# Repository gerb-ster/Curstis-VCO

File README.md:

# Curtis-VCO

This module is based on the classic CEM3340 VCO chip, although I’m using a AS3340 clone. I’ve took some inspiration from the Maximus VCO design from Thomas Henry. The CEM3340 outputs 3 waveforms with different output levels. To achieve a uniform 10 vpp output around 0 volt, I used a series of op-amps. In the first step the 3 levels is attenuated to 10 vpp, in the next step it’s being offset with 5v to make it swing around 0 volt. I’ve used a trimpot to fine-tune the offset.

The triangle output is then used to ‘wave shape’ a sine output. For this, I also used a classic design from Thomas.

I’ve already made some changes to the PCB design, there was an issue with the power rails on the IO board (hence the bodge wire), some transistor values where wrong, and I made some more room for a good timing cap.

### Update 18-05-2022

Small changes have been made to the io-board to fix an issue with PWM range knob. If you have an older board, you can remove R51 from the ioboard and replace it with a wire and replace R49 with a 91k resistor.

## Status: Finished

- done: first schematic & board design
- done: breadboard and test
- done: design frontpanel
- done: order PCB and build prototype

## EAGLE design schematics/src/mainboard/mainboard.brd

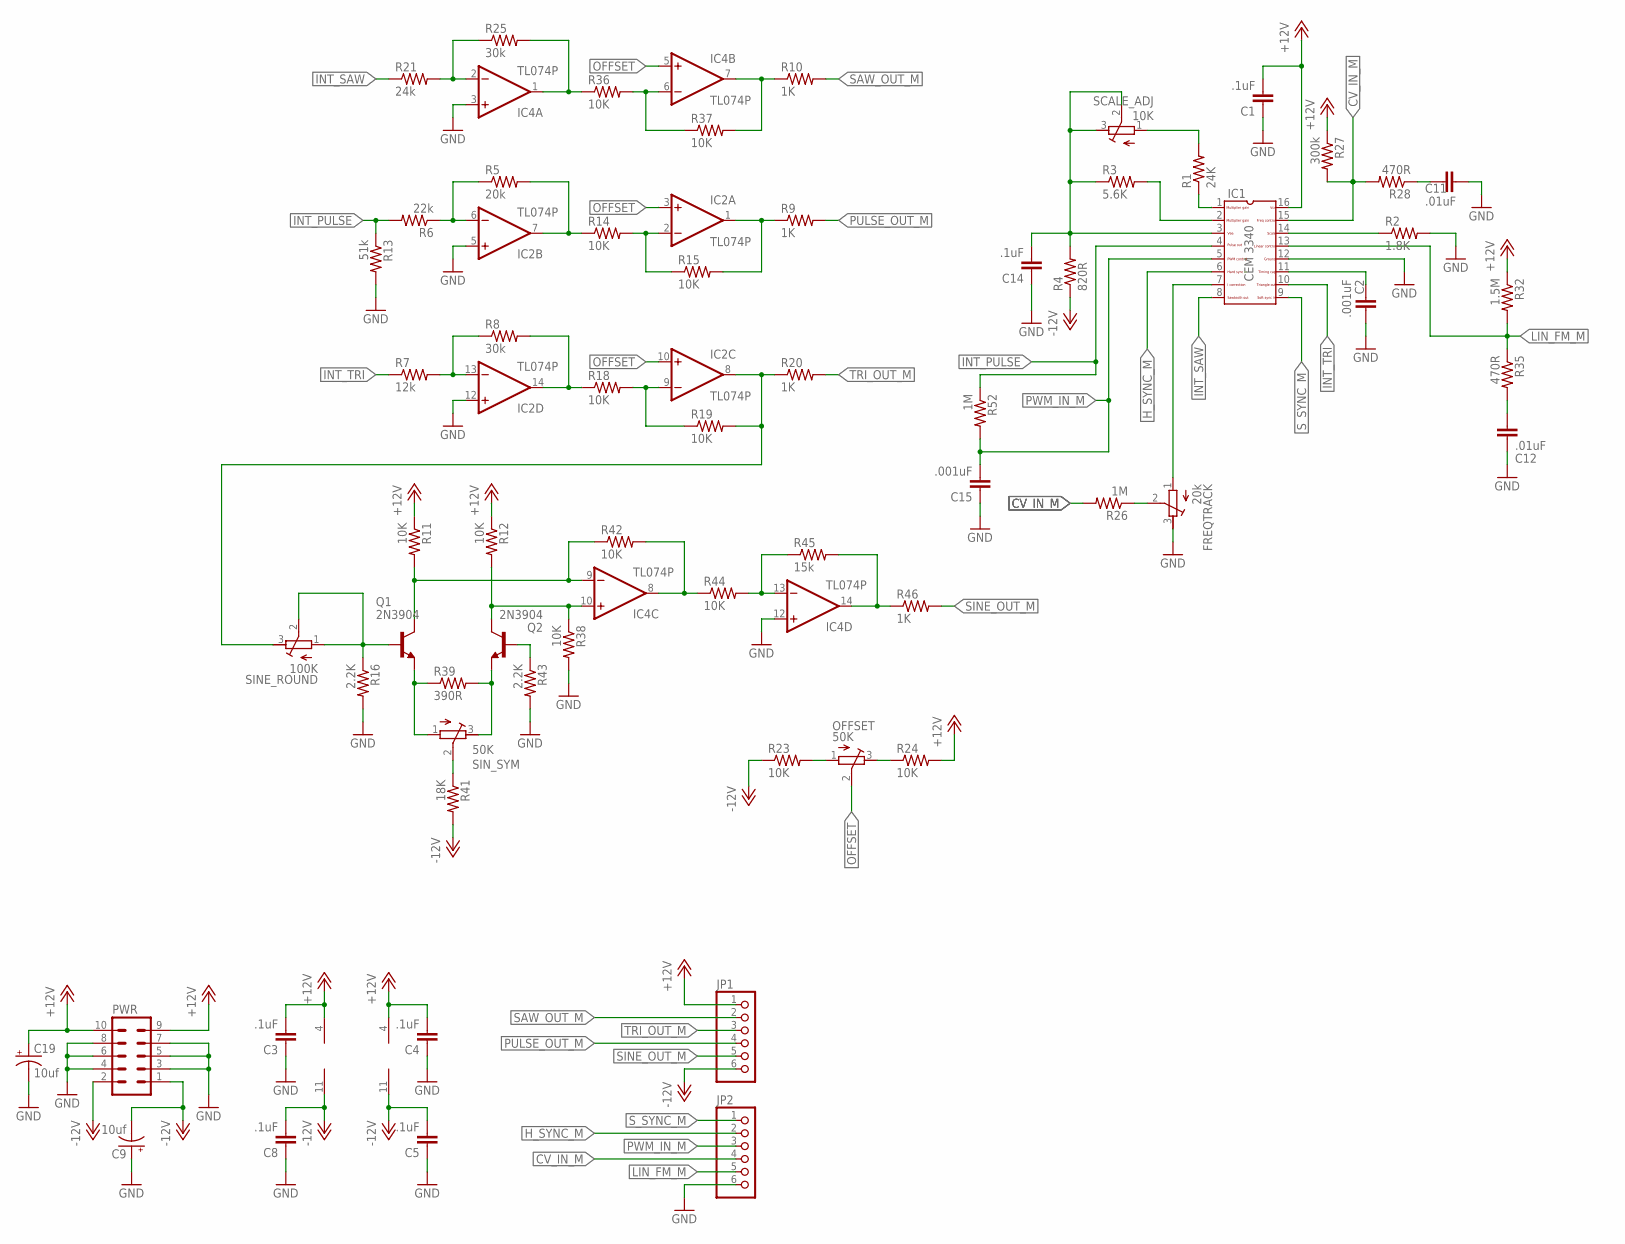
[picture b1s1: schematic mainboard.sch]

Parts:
C1, C3, C4, C5, C8, C14: .1uF; C050-024X044
C2: .001uF; C150-054X183
C9, C19: 10uf; E2,5-5
C11, C12: .01uF; C050-024X044
C15: .001uF; C050-024X044
FREQTRACK: 20k; RTRIM3296W
IC1: CEM3340; DIL16
IC2, IC4: TL074P; DIL14
JP1, JP2: PINHD-1X6; 1X06
OFFSET: 50K; RTRIM3296W
PWR: ML10
Q1, Q2: 2N3904; TO92
R1: 24K; 0207/7
R2: 1.8K; 0207/7
R3: 5.6K; 0207/7
R4: 820R; 0207/7
R5: 20k; 0207/7
R6: 22k; 0207/7
R7: 12k; 0207/7
R8, R25: 30k; 0207/7
R9, R10, R20, R46: 1K; 0207/7
R11, R12, R14, R15, R18, R19, R23, R24, R36, R37, R38, R42, R44: 10K; 0207/7
R13: 51k; 0207/7
R16, R43: 2.2K; 0207/7
R21: 24k; 0207/7
R26, R52: 1M; 0207/7
R27: 300k; 0207/7
R28, R35: 470R; 0207/7
R32: 1.5M; 0207/7
R39: 390R; 0207/7
R41: 18K; 0207/7
R45: 15k; 0207/7
SCALE_ADJ: 10K; RTRIM3296W
SINE_ROUND: 100K; RTRIM3296W
SIN_SYM: 50K; RTRIM3296W

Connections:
+12V: C1.2, C3.2, C4.2, C19.+, IC1.16, IC2.4 (V+), IC4.4 (V+), JP1.1, PWR.9, PWR.10, R11.1, R12.1, R24.2, R27.1, R32.1
-12V: C5.2, C8.2, C9.-, IC2.11 (V-), IC4.11 (V-), JP1.6, PWR.1, PWR.2, R4.1, R23.1, R41.2
CV_IN_M: IC1.15, JP2.4, R26.2, R27.2, R28.2
GND: C1.1, C2.2, C3.1, C4.1, C5.1, C8.1, C9.+, C11.1, C12.2, C14.1, C15.1, C19.-, FREQTRACK.3 (E), IC1.12, IC2.5 (+IN), IC2.12 (+IN), IC4.3 (+IN), IC4.12 (+IN), JP2.6, PWR.3, PWR.4, PWR.5, PWR.6, PWR.7, PWR.8, R2.2, R13.2, R16.2, R38.2, R43.2
HF_CORRECTION: FREQTRACK.1 (A), IC1.7
H_SYNC_M: IC1.6, JP2.2
INT_PULSE: IC1.4, R6.2, R13.1, R52.1
INT_SAW: IC1.8, R21.1
INT_TRI: IC1.10, R7.1
LIN_FM_M: IC1.13, JP2.5, R32.2, R35.1
unnamed: IC1.1, R1.1
unnamed: C2.1, IC1.11
unnamed: IC1.14, R2.1
unnamed: IC1.2, R3.2
unnamed: Q1.2 (B), R16.1, SINE_ROUND.1 (A), SINE_ROUND.2 (S)
unnamed: IC2.6 (-IN), R5.1, R6.1
unnamed: C14.2, IC1.3, R3.1, R4.2, SCALE_ADJ.2 (S), SCALE_ADJ.3 (E)
unnamed: R1.2, SCALE_ADJ.1 (A)
unnamed: IC4.1 (OUT), R25.2, R36.1
unnamed: IC4.9 (-IN), Q1.1 (C), R11.2, R42.1
unnamed: IC2.13 (-IN), R7.2, R8.1
unnamed: IC4.10 (+IN), Q2.1 (C), R12.2, R38.1
unnamed: IC2.14 (OUT), R8.2, R18.1
unnamed: IC2.7 (OUT), R5.2, R14.1
unnamed: IC2.2 (-IN), R14.2, R15.1
unnamed: R41.1, SIN_SYM.2 (S)
unnamed: Q1.3 (E), R39.1, SIN_SYM.1 (A)
unnamed: IC2.9 (-IN), R18.2, R19.1
unnamed: OFFSET.1 (A), R23.2
unnamed: OFFSET.3 (E), R24.1
unnamed: FREQTRACK.2 (S), R26.1
unnamed: C11.2, R28.1
unnamed: IC2.1 (OUT), R9.1, R15.2
unnamed: IC4.6 (-IN), R36.2, R37.1
unnamed: C12.1, R35.2
unnamed: IC2.8 (OUT), R19.2, R20.1, SINE_ROUND.3 (E)
unnamed: Q2.3 (E), R39.2, SIN_SYM.3 (E)
unnamed: IC4.2 (-IN), R21.2, R25.1
unnamed: IC4.8 (OUT), R42.2, R44.1
unnamed: IC4.7 (OUT), R10.1, R37.2
unnamed: Q2.2 (B), R43.1
unnamed: IC4.14 (OUT), R45.2, R46.1
unnamed: IC4.13 (-IN), R44.2, R45.1
OFFSET: IC2.3 (+IN), IC2.10 (+IN), IC4.5 (+IN), OFFSET.2 (S)
PULSE_OUT_M: JP1.4, R9.2
PWM_IN_M: C15.2, IC1.5, JP2.3, R52.2
SAW_OUT_M: JP1.2, R10.2
SINE_OUT_M: JP1.5, R46.2
S_SYNC_M: IC1.9, JP2.1
TRI_OUT_M: JP1.3, R20.2

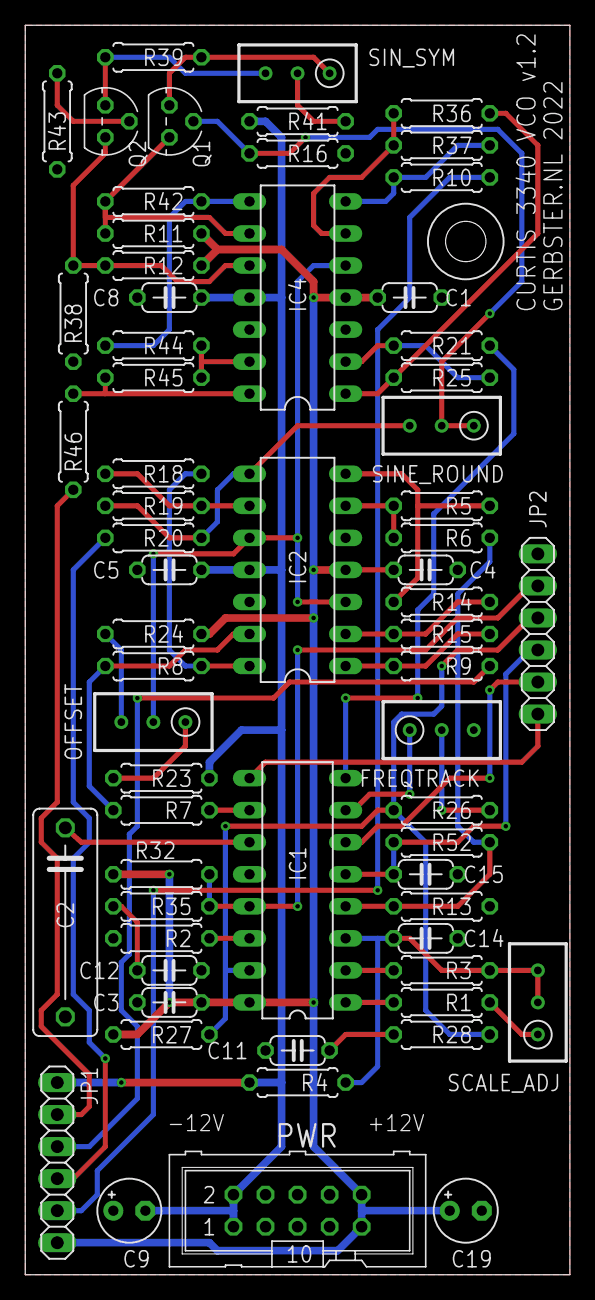
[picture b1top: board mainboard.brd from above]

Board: 2 copper layers, 43.2 x 99.1 mm, 64 parts (0 on the bottom side), 50 nets.

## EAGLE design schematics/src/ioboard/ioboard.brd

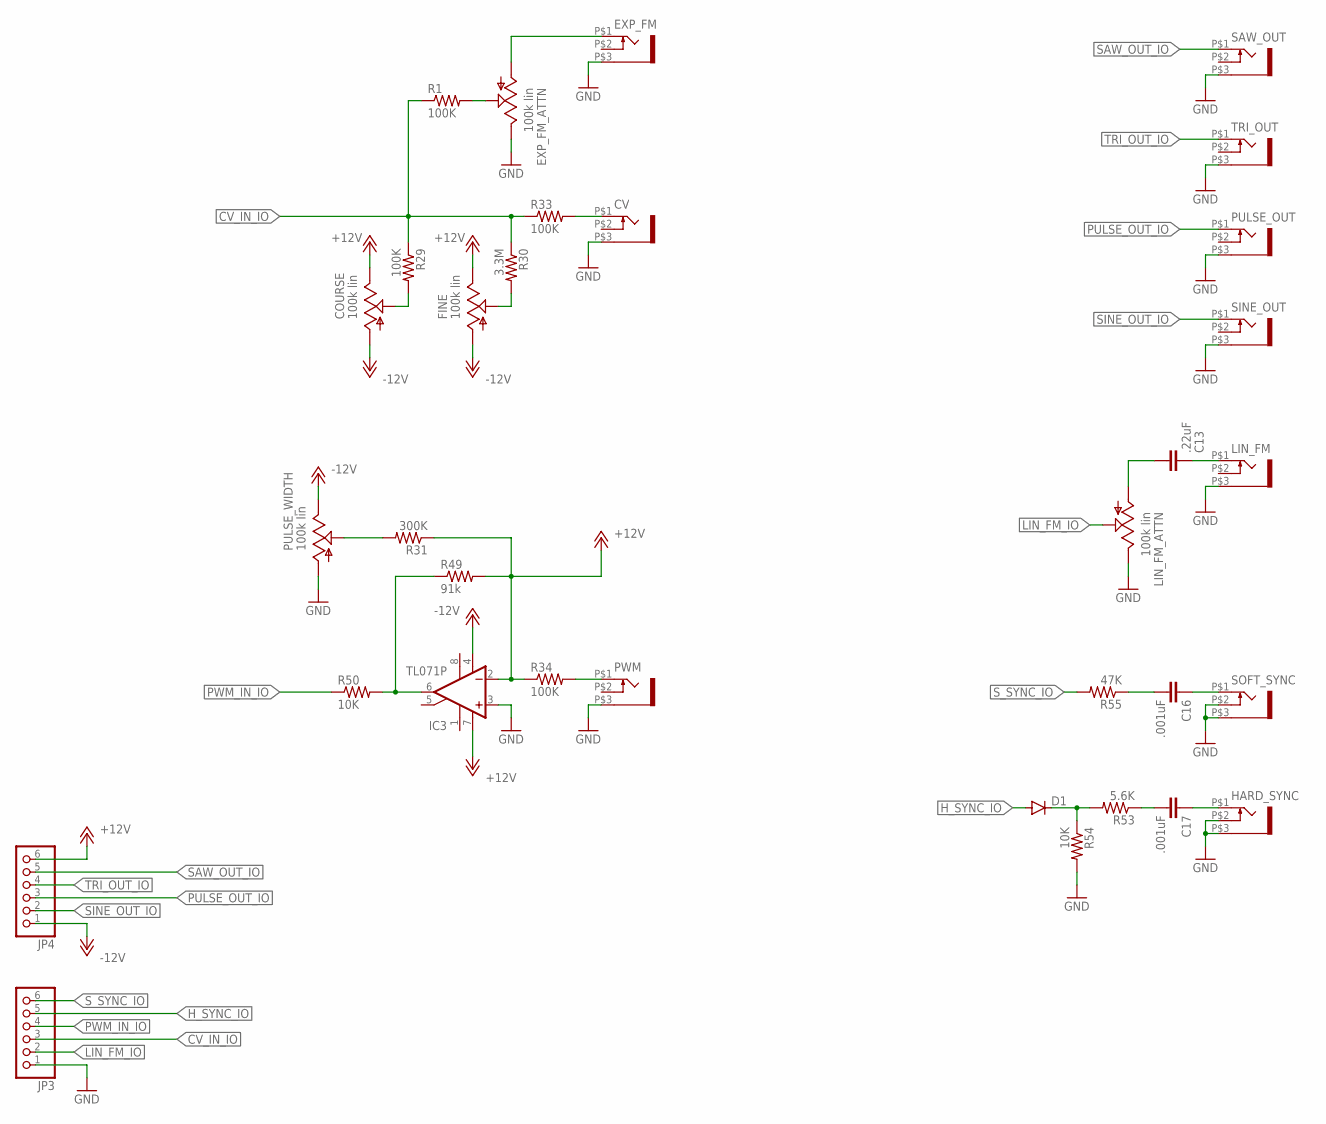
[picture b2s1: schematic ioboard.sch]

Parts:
C13: .22uF; C050-024X044
C16, C17: .001uF; C050-024X044
COURSE: 100k lin; EVUF
CV: WQP-PJ301M-12_JACK
D1: 1N4148DO35-7; DO35-7
EXP_FM: WQP-PJ301M-12_JACK
EXP_FM_ATTN: 100k lin; EVUF
FINE: 100k lin; EVUF
HARD_SYNC: WQP-PJ301M-12_JACK
IC3: TL071P; DIL08
JP3, JP4: PINHD-1X6; 1X06
LIN_FM: WQP-PJ301M-12_JACK
LIN_FM_ATTN: 100k lin; EVUF
PULSE_OUT: WQP-PJ301M-12_JACK
PULSE_WIDTH: 100k lin; EVUF
PWM: WQP-PJ301M-12_JACK
R1, R29, R33, R34: 100K; 0207/7
R30: 3.3M; 0207/7
R31: 300K; 0207/7
R49: 91k; 0207/7
R50, R54: 10K; 0207/7
R53: 5.6K; 0207/7
R55: 47K; 0207/7
SAW_OUT: WQP-PJ301M-12_JACK
SINE_OUT: WQP-PJ301M-12_JACK
SOFT_SYNC: WQP-PJ301M-12_JACK
TRI_OUT: WQP-PJ301M-12_JACK

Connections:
+12V: COURSE.3 (E), FINE.3 (E), IC3.2 (-IN), IC3.7 (V+), JP4.6, R31.1, R34.1, R49.2
-12V: COURSE.1 (A), FINE.1 (A), IC3.4 (V-), JP4.1, PULSE_WIDTH.3 (E)
CV_IN_IO: JP3.3, R1.1, R29.1, R30.1, R33.1
GND: CV.P$3 (1), EXP_FM.P$3 (1), EXP_FM_ATTN.3 (E), HARD_SYNC.P$2 (3), HARD_SYNC.P$3 (1), IC3.3 (+IN), JP3.1, LIN_FM.P$3 (1), LIN_FM_ATTN.3 (E), PULSE_OUT.P$3 (1), PULSE_WIDTH.1 (A), PWM.P$3 (1), R54.2, SAW_OUT.P$3 (1), SINE_OUT.P$3 (1), SOFT_SYNC.P$2 (3), SOFT_SYNC.P$3 (1), TRI_OUT.P$3 (1)
H_SYNC_IO: D1.A, JP3.5
LIN_FM_IO: EXP_FM_ATTN.2 (S), JP3.2, LIN_FM_ATTN.2 (S), R1.2
unnamed: EXP_FM.P$1 (2), EXP_FM_ATTN.1 (A)
unnamed: COURSE.2 (S), R29.2
unnamed: FINE.2 (S), R30.2
unnamed: CV.P$1 (2), R33.2
unnamed: PWM.P$1 (2), R34.2
unnamed: PULSE_WIDTH.2 (S), R31.2
unnamed: C13.2, LIN_FM.P$1 (2)
unnamed: C13.1, LIN_FM_ATTN.1 (A)
unnamed: C16.1, SOFT_SYNC.P$1 (2)
unnamed: IC3.6 (OUT), R49.1, R50.2
unnamed: C16.2, R55.1
unnamed: C17.1, HARD_SYNC.P$1 (2)
unnamed: C17.2, R53.1
unnamed: D1.C, R53.2, R54.1
PULSE_OUT_IO: JP4.3, PULSE_OUT.P$1 (2)
PWM_IN_IO: JP3.4, R50.1
SAW_OUT_IO: JP4.5, SAW_OUT.P$1 (2)
SINE_OUT_IO: JP4.2, SINE_OUT.P$1 (2)
S_SYNC_IO: JP3.6, R55.2
TRI_OUT_IO: JP4.4, TRI_OUT.P$1 (2)

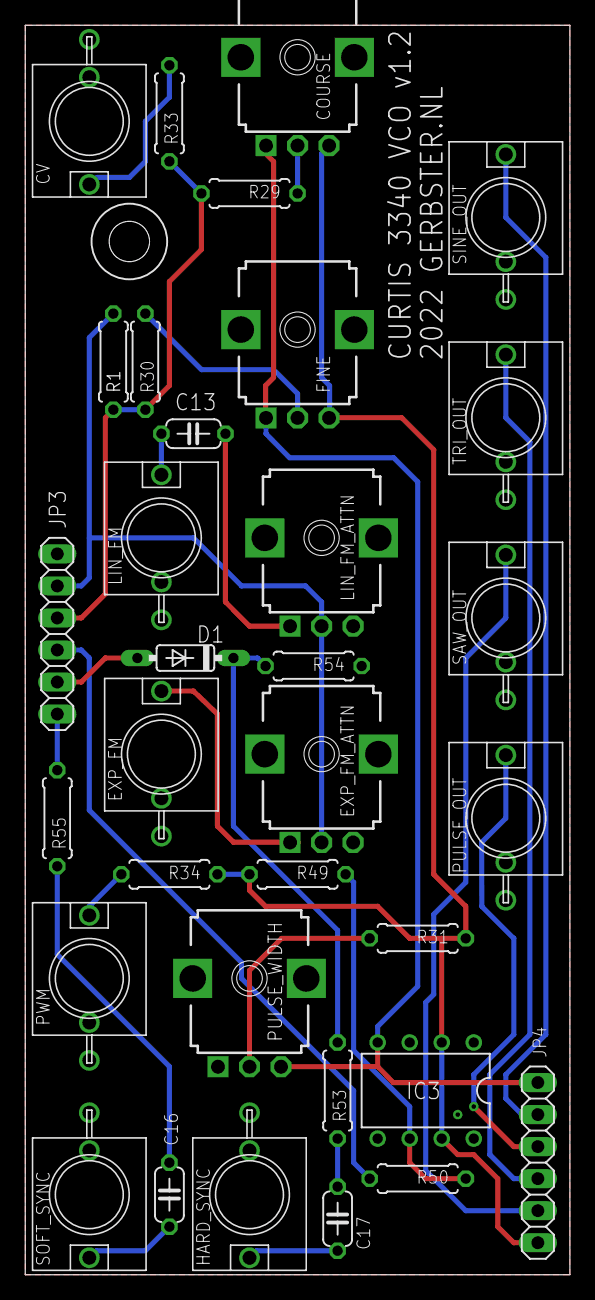
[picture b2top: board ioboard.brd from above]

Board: 2 copper layers, 43.2 x 99.1 mm, 33 parts (0 on the bottom side), 26 nets.

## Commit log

2021-04-18 Create readme.md
    initial commit
2021-04-18 Add PDF files and restructured
2021-04-27 done
2021-04-27 no message
2021-04-27 added disclaimer text
2021-04-27 Added faceplate designs
2021-05-07 Added files and structure
2021-05-07 small typos
2021-05-10 Added Status
2021-05-10 re-added README.md file
2021-05-11 Added Status & Images
2021-06-15 Updated Schematics, Fixed Power Socket orientation
2021-08-06 Updated some schematics and docs
2022-05-04 Fixed schematics & descriptions
2022-05-17 Updated Firmware
2022-05-18 Updated Faceplates
2022-05-18 Fixed issues
2022-05-21 Fixed schematics
2022-05-28 General updates
